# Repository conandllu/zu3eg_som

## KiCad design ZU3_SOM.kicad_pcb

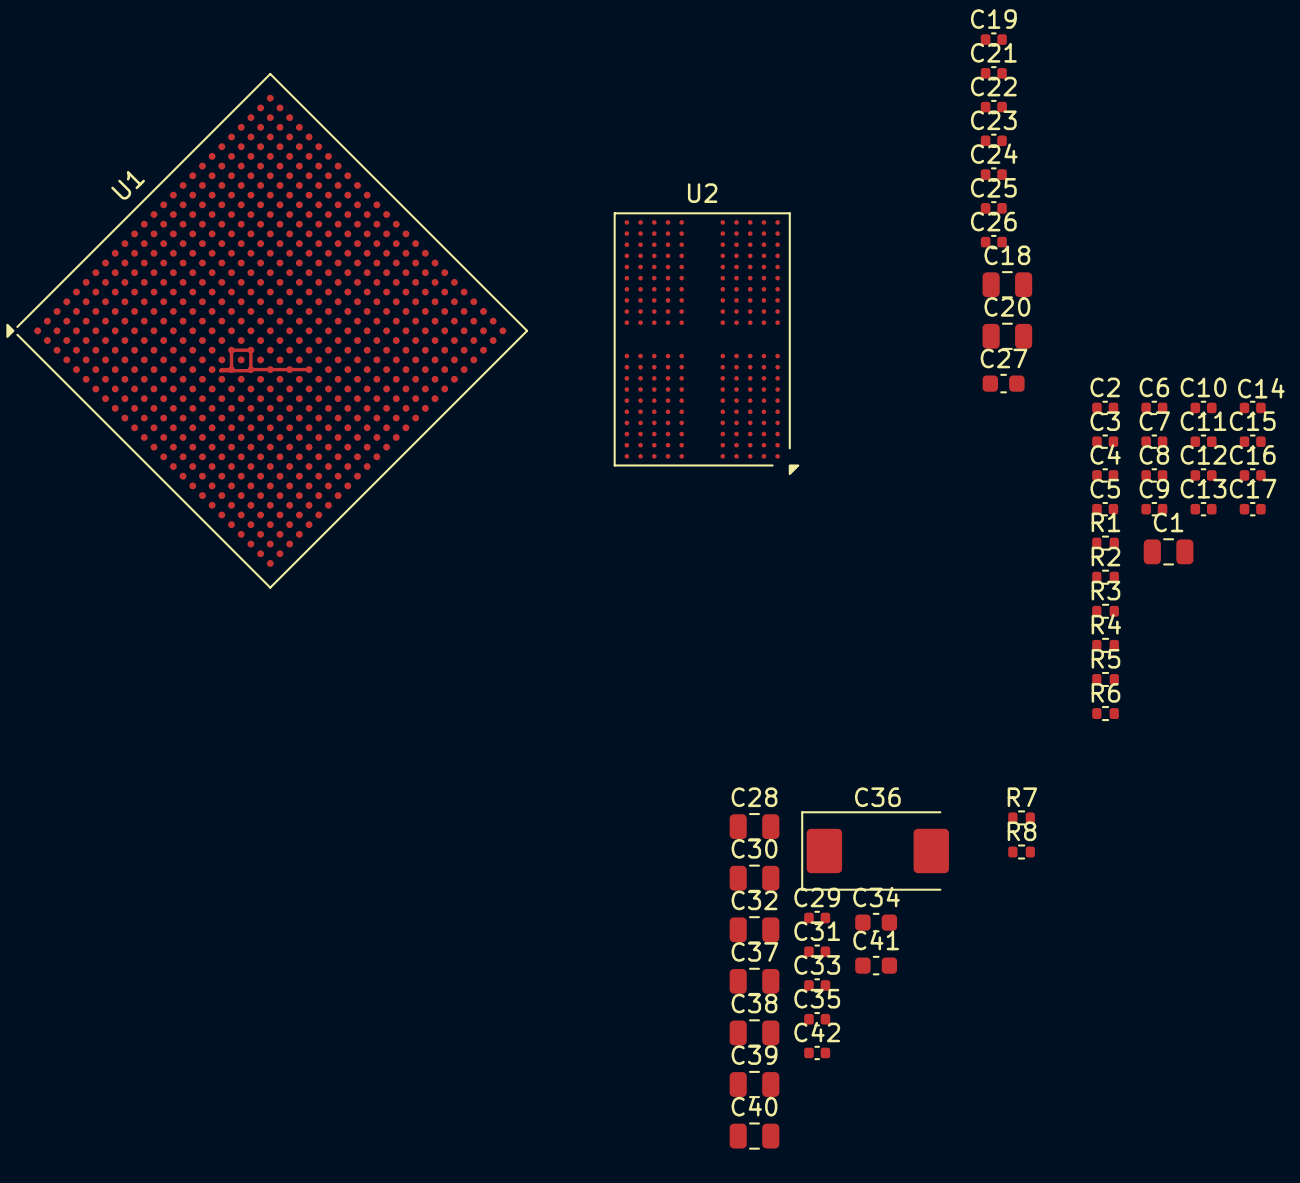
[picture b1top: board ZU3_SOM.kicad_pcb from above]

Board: 2 copper layers, 52 parts (0 on the bottom side), 80 nets.

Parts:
C1, C18, C20, C28, C30, C32, C37, C38, C39, C40: 100uF/6.3V; C_0805_2012Metric
C2, C3, C19, C21, C22, C24, C26, C29, C31, C33, C35, C42: 10uF/6.3V; C_0402_1005Metric
C4, C5: 100nF/16V; C_0402_1005Metric
C6, C9: 47nF/50V; C_0402_1005Metric
C7, C8: 470nF/10V; C_0402_1005Metric
C10, C11, C12, C13, C14, C15, C16, C17: 1nF/50V; C_0402_1005Metric
C23, C25: 10nF/50V; C_0402_1005Metric
C27, C34, C41: 47uF/6.3V; C_0603_1608Metric
C36: 330uF/2V; CP_EIA-7343-20_Kemet-V
R1, R2: 10K; R_0402_1005Metric
R3, R4, R5: 240; R_0402_1005Metric
R6: 4K7; R_0402_1005Metric
R7, R8: 1K; R_0402_1005Metric
U1: ZU3EGSFVA625; BGA-625_21.0x21.0mm_Layout25x25_P0.8mm
U2: MT53D512M32D2DS-053 WT:D; BGA-200_10x14.5mm_Layout12x22_P0.8x0.65mm

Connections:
/ZU3_DDR/PS_DDR_A_D0: U1.AB15 (PS_DDR_DQ0), U2.B2 (DQ0_A)
/ZU3_DDR/PS_DDR_A_D1: U1.AE15 (PS_DDR_DQ1), U2.C2 (DQ1_A)
/ZU3_DDR/PS_DDR_A_D2: U1.AC15 (PS_DDR_DQ2), U2.E2 (DQ2_A)
/ZU3_DDR/PS_DDR_A_D3: U1.AE14 (PS_DDR_DQ3), U2.F2 (DQ3_A)
/ZU3_DDR/PS_DDR_A_D4: U1.AD13 (PS_DDR_DQ4), U2.F4 (DQ4_A)
/ZU3_DDR/PS_DDR_A_D5: U1.AC13 (PS_DDR_DQ5), U2.E4 (DQ5_A)
/ZU3_DDR/PS_DDR_A_D6: U1.AB13 (PS_DDR_DQ6), U2.C4 (DQ6_A)
/ZU3_DDR/PS_DDR_A_D7: U1.AA13 (PS_DDR_DQ7), U2.B4 (DQ7_A)
/ZU3_DDR/PS_DDR_A_D8: U1.AC16 (PS_DDR_DQ8), U2.B11 (DQ8_A)
/ZU3_DDR/PS_DDR_A_D9: U1.AB16 (PS_DDR_DQ9), U2.C11 (DQ9_A)
/ZU3_DDR/PS_DDR_A_D10: U1.AD16 (PS_DDR_DQ10), U2.E11 (DQ10_A)
/ZU3_DDR/PS_DDR_A_D11: U1.AE16 (PS_DDR_DQ11), U2.F11 (DQ11_A)
/ZU3_DDR/PS_DDR_A_D12: U1.AE19 (PS_DDR_DQ12), U2.F9 (DQ12_A)
/ZU3_DDR/PS_DDR_A_D13: U1.AD18 (PS_DDR_DQ13), U2.E9 (DQ13_A)
/ZU3_DDR/PS_DDR_A_D14: U1.AB18 (PS_DDR_DQ14), U2.C9 (DQ14_A)
/ZU3_DDR/PS_DDR_A_D15: U1.AC18 (PS_DDR_DQ15), U2.B9 (DQ15_A)
/ZU3_DDR/PS_DDR_A_DQS0_C: U1.AD14 (PS_DDR_DQS_N0), U2.E3 (DQS0_C_A)
/ZU3_DDR/PS_DDR_A_DQS0_T: U1.AC14 (PS_DDR_DQS_P0), U2.D3 (DQS0_T_A)
/ZU3_DDR/PS_DDR_A_DQS1_C: U1.AE17 (PS_DDR_DQS_N1), U2.E10 (DQS1_C_A)
/ZU3_DDR/PS_DDR_A_DQS1_T: U1.AD17 (PS_DDR_DQS_P1), U2.D10 (DQS1_T_A)
/ZU3_DDR/PS_DDR_B_D0: U1.W18 (PS_DDR_DQ16), U2.AA2 (DQ0_B)
/ZU3_DDR/PS_DDR_B_D1: U1.Y19 (PS_DDR_DQ17), U2.Y2 (DQ1_B)
/ZU3_DDR/PS_DDR_B_D2: U1.AA19 (PS_DDR_DQ18), U2.V2 (DQ2_B)
/ZU3_DDR/PS_DDR_B_D3: U1.W16 (PS_DDR_DQ19), U2.U2 (DQ3_B)
/ZU3_DDR/PS_DDR_B_D4: U1.AA18 (PS_DDR_DQ20), U2.U4 (DQ4_B)
/ZU3_DDR/PS_DDR_B_D5: U1.AA15 (PS_DDR_DQ21), U2.V4 (DQ5_B)
/ZU3_DDR/PS_DDR_B_D6: U1.Y16 (PS_DDR_DQ22), U2.Y4 (DQ6_B)
/ZU3_DDR/PS_DDR_B_D7: U1.Y15 (PS_DDR_DQ23), U2.AA4 (DQ7_B)
/ZU3_DDR/PS_DDR_B_D8: U1.AE20 (PS_DDR_DQ24), U2.AA11 (DQ8_B)
/ZU3_DDR/PS_DDR_B_D9: U1.AD19 (PS_DDR_DQ25), U2.Y11 (DQ9_B)
/ZU3_DDR/PS_DDR_B_D10: U1.AB20 (PS_DDR_DQ26), U2.V11 (DQ10_B)
/ZU3_DDR/PS_DDR_B_D11: U1.AC19 (PS_DDR_DQ27), U2.U11 (DQ11_B)
/ZU3_DDR/PS_DDR_B_D12: U1.AE21 (PS_DDR_DQ28), U2.U9 (DQ12_B)
/ZU3_DDR/PS_DDR_B_D13: U1.AB21 (PS_DDR_DQ29), U2.V9 (DQ13_B)
/ZU3_DDR/PS_DDR_B_D14: U1.AE22 (PS_DDR_DQ30), U2.Y9 (DQ14_B)
/ZU3_DDR/PS_DDR_B_D15: U1.AD22 (PS_DDR_DQ31), U2.AA9 (DQ15_B)
/ZU3_DDR/PS_DDR_B_DQS0_C: U1.AA17 (PS_DDR_DQS_N2), U2.V3 (DQS0_C_B)
/ZU3_DDR/PS_DDR_B_DQS0_T: U1.Y17 (PS_DDR_DQS_P2), U2.W3 (DQS0_T_B)
/ZU3_DDR/PS_DDR_B_DQS1_C: U1.AC21 (PS_DDR_DQS_N3), U2.V10 (DQS1_C_B)
/ZU3_DDR/PS_DDR_B_DQS1_T: U1.AC20 (PS_DDR_DQS_P3), U2.W10 (DQS1_T_B)
/ZU3_DDR/PS_DDR_CAA0: U1.U25 (PS_DDR_A0), U2.H2 (CA0_A)
/ZU3_DDR/PS_DDR_CAA1: U1.Y25 (PS_DDR_A1), U2.J2 (CA1_A)
/ZU3_DDR/PS_DDR_CAA2: U1.AB25 (PS_DDR_A2), U2.H9 (CA2_A)
/ZU3_DDR/PS_DDR_CAA3: U1.AA25 (PS_DDR_A3), U2.H10 (CA3_A)
/ZU3_DDR/PS_DDR_CAA4: U1.V25 (PS_DDR_A4), U2.H11 (CA4_A)
/ZU3_DDR/PS_DDR_CAA5: U1.AC25 (PS_DDR_A5), U2.J11 (CA5_A)
/ZU3_DDR/PS_DDR_CAB0: U1.AB23 (PS_DDR_A10), U2.R2 (CA0_B)
/ZU3_DDR/PS_DDR_CAB1: U1.AD24 (PS_DDR_A11), U2.P2 (CA1_B)
/ZU3_DDR/PS_DDR_CAB2: U1.AC23 (PS_DDR_A12), U2.R9 (CA2_B)
/ZU3_DDR/PS_DDR_CAB3: U1.AE24 (PS_DDR_A13), U2.R10 (CA3_B)
/ZU3_DDR/PS_DDR_CAB4: U1.AC24 (PS_DDR_A14), U2.R11 (CA4_B)
/ZU3_DDR/PS_DDR_CAB5: U1.AD23 (PS_DDR_A15), U2.P11 (CA5_B)
/ZU3_DDR/PS_DDR_CKA_C: U1.AA24 (PS_DDR_CK_N0), U2.J9 (CK_C_A)
/ZU3_DDR/PS_DDR_CKA_T: U1.AA23 (PS_DDR_CK0), U2.J8 (CK_T_A)
/ZU3_DDR/PS_DDR_CKB_C: U1.AA22 (PS_DDR_CK_N1), U2.P9 (CK_C_B)
/ZU3_DDR/PS_DDR_CKB_T: U1.Y22 (PS_DDR_CK1), U2.P8 (CK_T_B)
/ZU3_DDR/PS_DDR_CKE0: U1.T24 (PS_DDR_CKE0), U2.J4 (CKE0_A), U2.P4 (CKE0_B)
/ZU3_DDR/PS_DDR_CKE1: U1.W24 (PS_DDR_CKE1), U2.J5 (NC_J5), U2.P5 (NC_P5)
/ZU3_DDR/PS_DDR_CS0_N: U1.T25 (PS_DDR_CS_N0), U2.H4 (CS0_A), U2.R4 (CS0_B)
/ZU3_DDR/PS_DDR_CS1_N: U1.W23 (PS_DDR_CS_N1), U2.H3 (NC_H3), U2.R3 (NC_R3)
/ZU3_DDR/PS_DDR_DMI0_A: U1.AA14 (PS_DDR_DM0), U2.C3 (DMI0_A)
/ZU3_DDR/PS_DDR_DMI0_B: U1.W17 (PS_DDR_DM2), U2.Y3 (DMI0_B)
/ZU3_DDR/PS_DDR_DMI1_A: U1.AB17 (PS_DDR_DM1), U2.C10 (DMI1_A)
/ZU3_DDR/PS_DDR_DMI1_B: U1.AD21 (PS_DDR_DM3), U2.Y10 (DMI1_B)
/ZU3_DDR/PS_DDR_RST_N: R6.2, U1.U21 (PS_DDR_RAM_RST_N), U2.T11 (RESET_N)
GND: C1.1, C2.1, C3.2, C4.2, C5.2, C6.2, C7.2, C8.2, C9.2, C10.2, C11.2, C12.2, C13.2, C14.2, C15.2, C16.1, C17.1, C18.2, C19.2, C20.2, C21.2, C22.2, C23.2, C24.2, C25.2, C26.2, C27.2, C28.1, C29.1, C30.1, C31.1, C32.1, C33.1, C34.1, C35.1, C36.2, C37.1, C38.1, C39.1, C40.1, C41.1, C42.1, R3.1, R6.1, R8.2, U1.A1 (GND), U1.A11 (GND), U1.A16 (GND), U1.A21 (GND), U1.A25 (GND), U1.AA1 (GND), U1.AA11 (GND), U1.AA16 (GND), U1.AB4 (GND), U1.AB14 (GND), U1.AB19 (GND), U1.AC2 (GND), U1.AC7 (GND), U1.AC12 (GND), U1.AC22 (GND), U1.AD10 (GND), U1.AD15 (GND), U1.AD25 (GND), U1.AE5 (GND), U1.AE8 (GND), U1.AE13 (GND), U1.AE18 (GND), U1.AE23 (GND), U1.B4 (GND), U1.B9 (GND), U1.B14 (GND), U1.B19 (GND), U1.B21 (GND), U1.B23 (GND), U1.C2 (GND), U1.C7 (GND), U1.C12 (GND), U1.C17 (GND), U1.C21 (GND), U1.C24 (GND), U1.C25 (GND), U1.D21 (GND), U1.D23 (GND), U1.E3 (GND), U1.E21 (GND), U1.E24 (GND), U1.E25 (GND), U1.F1 (GND), U1.F6 (GND), U1.F16 (GND), U1.F21 (GND), U1.F23 (GND), U1.G9 (GND), U1.G21 (GND), U1.G24 (GND), U1.G25 (GND), U1.H2 (GND), U1.H7 (GND), U1.H12 (GND), U1.H17 (GND), U1.H21 (GND), U1.H23 (GND), U1.J5 (GND), U1.J9 (GND), U1.J11 (GND), U1.J13 (GND), U1.J15 (GND), U1.J21 (GND), U1.J24 (GND), U1.J25 (GND), U1.K3 (GND), U1.K8 (GND), U1.K10 (GND), U1.K12 (GND), U1.K14 (GND), U1.K21 (GND), U1.K23 (GND), U1.L1 (GND), U1.L11 (GND), U1.L13 (GND), U1.L16 (GND), U1.L21 (GND), U1.L24 (GND), U1.L25 (GND), U1.M4 (GND), U1.M10 (GND), U1.M14 (GND), U1.M19 (GND), U1.M21 (GND), U1.M22 (GND), U1.M23 (GND), U1.N2 (GND), U1.N7 (GND), U1.N9 (GND), U1.N11 (GND), U1.N17 (GND), U1.N23 (GND), U1.N24 (GND), U1.N25 (GND), U1.P10 (GND), U1.P14 (GND), U1.P16 (GND), U1.P20 (GND), U1.P25 (GND), U1.R3 (GND), U1.R11 (GND), U1.R18 (GND), U1.R23 (GND), U1.T1 (GND), U1.T6 (GND), U1.T8 (GND), U1.T10 (GND), U1.T12 (GND), U1.T14 (GND), U1.T16 (GND), U1.T21 (GND), U1.U11 (GND), U1.U13 (GND), U1.U19 (GND), U1.U24 (GND), U1.V2 (GND), U1.V9 (POR_OVERRIDE), U1.V17 (GND), U1.W5 (GND), U1.W20 (GND), U1.W25 (GND), U1.Y3 (GND), U1.Y8 (GND), U1.Y13 (GND), U1.Y23 (GND), U2.A3 (VSS), U2.A10 (VSS), U2.AB3 (VSS), U2.AB5 (VSS), U2.AB8 (VSS), U2.AB10 (VSS), U2.C1 (VSS), U2.C5 (VSS), U2.C8 (VSS), U2.C12 (VSS), U2.D2 (VSS), U2.D4 (VSS), U2.D9 (VSS), U2.D11 (VSS), U2.E1 (VSS), U2.E5 (VSS), U2.E8 (VSS), U2.E12 (VSS), U2.G1 (VSS), U2.G3 (VSS), U2.G5 (VSS), U2.G8 (VSS), U2.G10 (VSS), U2.G12 (VSS), U2.J1 (VSS), U2.J3 (VSS), U2.J10 (VSS), U2.J12 (VSS), U2.K2 (VSS), U2.K4 (VSS), U2.K9 (VSS), U2.K11 (VSS), U2.N2 (VSS), U2.N4 (VSS), U2.N9 (VSS), U2.N11 (VSS), U2.P1 (VSS), U2.P3 (VSS), U2.P10 (VSS), U2.P12 (VSS), U2.T1 (VSS), U2.T3 (VSS), U2.T5 (VSS), U2.T8 (VSS), U2.T10 (VSS), U2.T12 (VSS), U2.V1 (VSS), U2.V5 (VSS), U2.V8 (VSS), U2.V12 (VSS), U2.W2 (VSS), U2.W4 (VSS), U2.W9 (VSS), U2.W11 (VSS), U2.Y1 (VSS), U2.Y5 (VSS), U2.Y8 (VSS), U2.Y12 (VSS)
GND_ADC: U1.M12 (GNDADC), U1.N12 (VREFN), U1.P13 (VREFP)
unnamed: R7.1, R8.1, U1.V8 (PUDC_B)
unnamed: R3.2, U1.U22 (PS_DDR_ZQ)
unnamed: R5.1, U2.A8 (NC_A8)
unnamed: R1.2, U2.G2 (ODT_CA_A)
unnamed: R2.2, U2.T2 (ODT_CA_B)
unnamed: R4.1, U2.A5 (ZQ0)
PS_MGTRAVCC: C22.1, C23.1, U1.F22 (PS_MGTRAVCC), U1.H22 (PS_MGTRAVCC)
PS_MGTRAVTT: C24.1, C25.1, U1.A24 (PS_MGTRAVTT), U1.B22 (PS_MGTRAVTT), U1.D22 (PS_MGTRAVTT)
VCCO_PS_DDR: C1.2, C2.2, C3.1, C6.1, C7.1, C8.1, C9.1, C10.1, C11.1, C12.1, C13.1, C14.1, C15.1, C16.2, C17.2, R1.1, R2.1, R4.2, R5.2, U1.AA21 (VCCO_PSDDR_504), U1.AB24 (VCCO_PSDDR_504), U1.AC17 (VCCO_PSDDR_504), U1.AD20 (VCCO_PSDDR_504), U1.AE25 (VCCO_PSDDR_504), U1.V22 (VCCO_PSDDR_504), U1.Y18 (VCCO_PSDDR_504), U2.A4 (VDD2), U2.A9 (VDD2), U2.AA3 (VDDQ), U2.AA5 (VDDQ), U2.AA8 (VDDQ), U2.AA10 (VDDQ), U2.AB4 (VDD2), U2.AB9 (VDD2), U2.B3 (VDDQ), U2.B5 (VDDQ), U2.B8 (VDDQ), U2.B10 (VDDQ), U2.D1 (VDDQ), U2.D5 (VDDQ), U2.D8 (VDDQ), U2.D12 (VDDQ), U2.F3 (VDDQ), U2.F5 (VDD2), U2.F8 (VDD2), U2.F10 (VDDQ), U2.H1 (VDD2), U2.H5 (VDD2), U2.H8 (VDD2), U2.H12 (VDD2), U2.K1 (VDD2), U2.K3 (VDD2), U2.K10 (VDD2), U2.K12 (VDD2), U2.N1 (VDD2), U2.N3 (VDD2), U2.N10 (VDD2), U2.N12 (VDD2), U2.R1 (VDD2), U2.R5 (VDD2), U2.R8 (VDD2), U2.R12 (VDD2), U2.U3 (VDDQ), U2.U5 (VDD2), U2.U8 (VDD2), U2.U10 (VDDQ), U2.W1 (VDDQ), U2.W5 (VDDQ), U2.W8 (VDDQ), U2.W12 (VDDQ)
VCC_PL_INT: C34.2, C35.2, C36.1, C37.2, C38.2, C39.2, C40.2, C41.2, C42.2, U1.J10 (VCCINT), U1.J12 (VCCINT), U1.J14 (VCCINT), U1.K9 (VCCINT), U1.K11 (VCCINT), U1.K13 (VCCINT), U1.L10 (VCCINT), U1.L12 (VCCINT), U1.L14 (VCCINT), U1.M11 (VCCINT), U1.N8 (VCCINT_IO), U1.N10 (VCCINT), U1.N14 (VCCINT), U1.P8 (VCCINT_IO), U1.P9 (VCCBRAM), U1.P11 (VCCINT), U1.R8 (VCCINT_IO), U1.R9 (VCCBRAM), U1.R10 (VCCINT), U1.R14 (VCCINT), U1.T9 (VCCBRAM), U1.T11 (VCCINT), U1.T13 (VCCINT), U1.U8 (VCCINT_IO), U1.U9 (VCCBRAM), U1.U10 (VCCINT), U1.U12 (VCCINT), U1.U14 (VCCINT)
VCC_PS_AUX: C4.1, C5.1, C18.1, C19.1, C26.1, C27.1, R7.2, U1.J8 (VCCAUX_IO), U1.L8 (VCCAUX_IO), U1.L9 (VCCAUX), U1.M8 (VCCAUX_IO), U1.M9 (VCCAUX), U1.N15 (VCC_PSDDR_PLL), U1.N16 (VCC_PSDDR_PLL), U1.N18 (VCC_PSAUX), U1.P18 (VCC_PSAUX), U1.P19 (VCC_PSAUX), U1.R19 (VCC_PSAUX), U2.F1 (VDD1), U2.F12 (VDD1), U2.G4 (VDD1), U2.G9 (VDD1), U2.T4 (VDD1), U2.T9 (VDD1), U2.U1 (VDD1), U2.U12 (VDD1)
VCC_PS_INT: C28.2, C29.2, C30.2, C31.2, C32.2, C33.2, U1.P15 (VCC_PSINTLP), U1.P17 (VCC_PSINTLP), U1.R15 (VCC_PSINTLP), U1.R16 (VCC_PSINTLP), U1.R17 (VCC_PSINTLP), U1.R20 (VCC_PSINTFP_DDR), U1.T15 (VCC_PSINTFP), U1.T17 (VCC_PSINTLP), U1.T20 (VCC_PSINTFP_DDR), U1.U15 (VCC_PSINTFP), U1.U16 (VCC_PSINTFP), U1.U17 (VCC_PSINTFP), U1.U18 (VCC_PSINTFP), U1.U20 (VCC_PSINTFP_DDR), U1.V15 (VCC_PSINTFP), U1.V16 (VCC_PSINTFP)
VCC_PS_PLL: C20.1, C21.1, U1.M15 (VCC_PSPLL), U1.M16 (VCC_PSPLL), U1.M17 (VCC_PSPLL)

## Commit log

2025-11-04 add DDR 20251104
2025-11-04 update ddr 20251104a
2025-11-05 fix LPDDR4 lib info 20251105a
2025-11-05 20251105B
2025-11-05 update 20251106A
2025-11-06 updata 20251107A
2025-11-10 update 20251110A
2025-11-11 update 20251111A
2025-11-11 update 20251112a
2025-11-12 update 20251112b
2025-11-14 update 20251114a
2025-11-19 update 20251119a
2025-11-19 update 20251120a
2025-11-20 update 20251121a
2025-11-23 update 20251124a
